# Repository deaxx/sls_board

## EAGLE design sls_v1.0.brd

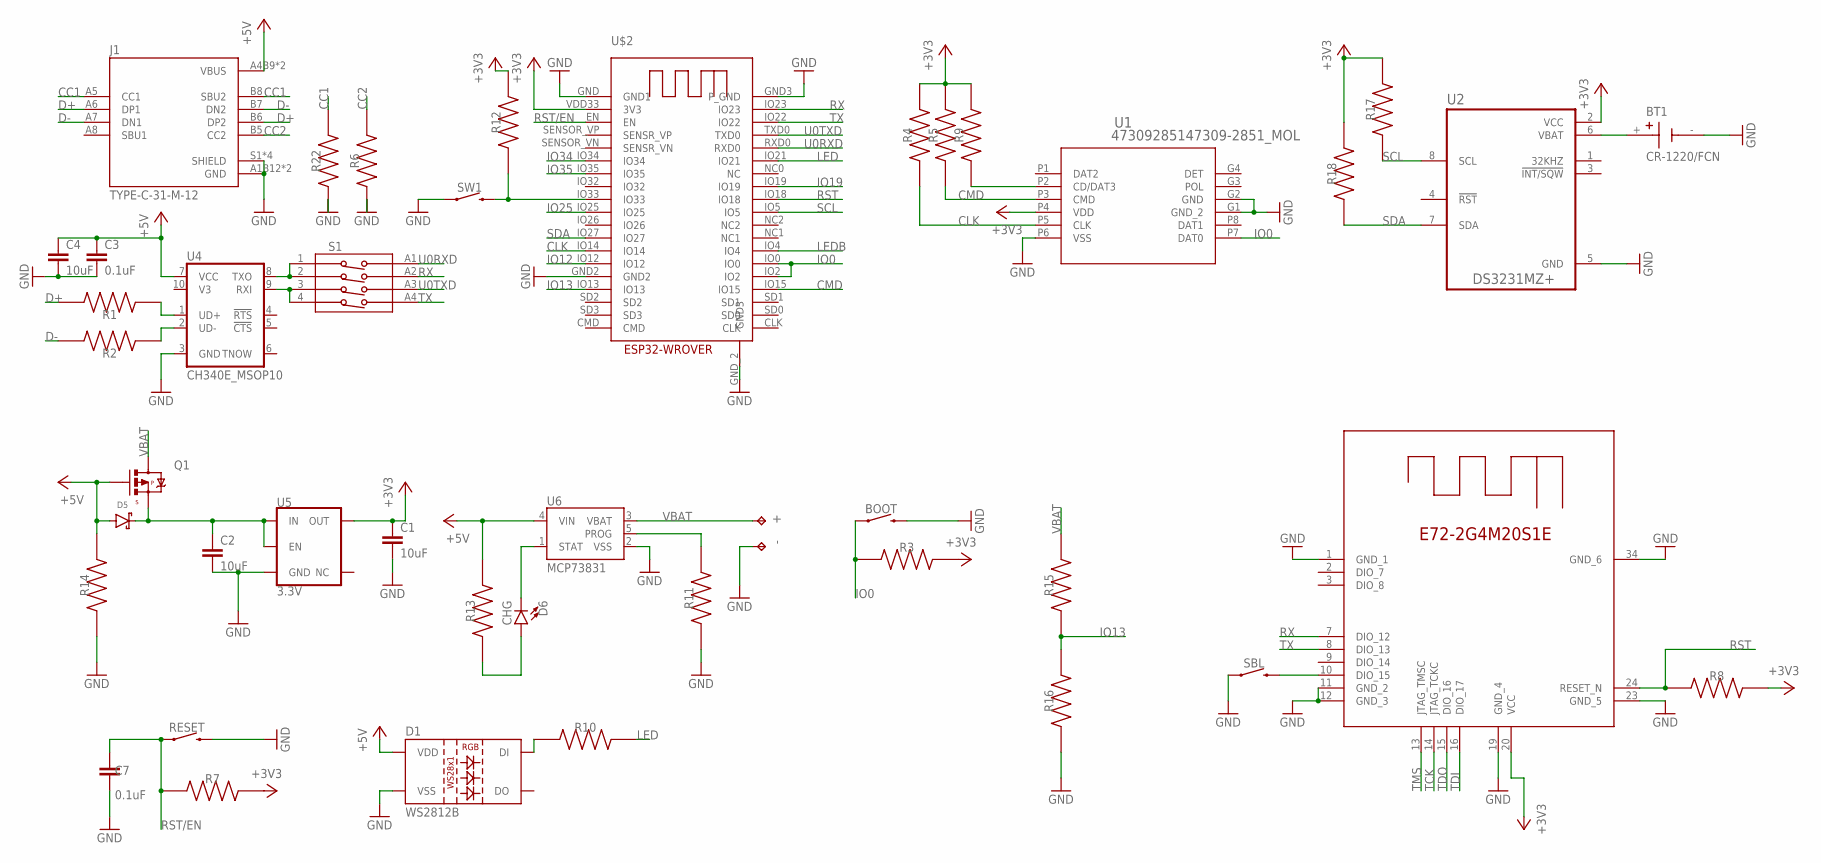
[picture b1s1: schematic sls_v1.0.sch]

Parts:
+: TPTP14R; TP14R
-: TPTP14R; TP14R
BOOT: MOMENTARY-SWITCH-SPST-SMD-4.6X2.8MM; TACTILE_SWITCH_SMD_4.6X2.8MM
BT1: CR-1220/FCN; BAT_CR-1220/FCN
C1, C2: 10uF; 0805
C3, C7: 0.1uF; 0603
C4: 10uF; 0603
D1: WS2812B
D5: DIODE-SCHOTTKY; SOD-323
D6: CHG; LED-0603
J1: TYPE-C-31-M-12; HRO_TYPE-C-31-M-12
Q1: MOSFET-PCHANNEL; SOT23
R1, R2, R3, R4, R5, R7, R9, R10, R12, R13, R14, R15, R16, R17, R18: RC0402FR-073M6L; RESC1005X40N
R6, R22: 5.1k; RESC1005X40N
R8: 100k; RESC1005X40N
R11: 2.7k; RESC1005X40N
RESET: MOMENTARY-SWITCH-SPST-SMD-4.6X2.8MM; TACTILE_SWITCH_SMD_4.6X2.8MM
S1: 416131160804
SBL: MOMENTARY-SWITCH-SPST-SMD-4.6X2.8MM; TACTILE_SWITCH_SMD_4.6X2.8MM
SW1: MOMENTARY-SWITCH-SPST-SMD-4.6X2.8MM; TACTILE_SWITCH_SMD_4.6X2.8MM
U1: 47309285147309-2851_MOL; 47309-2851_MOL
U2: DS3231MZ+; SOIC127P600X175-8N
U4: CH340E_MSOP10; MSOP10
U5: 3.3V; SOT23-5
U6: MCP73831; SOT23-5
U$1: E72-2G4M20S1E
U$2: ESP32-WROVER

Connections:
+3V3: C1.1, R3.2, R4.2, R5.2, R7.2, R8.2, R9.2, R12.2, R17.2, R18.2, U1.P4 (VDD), U2.2 (VCC), U5.5 (OUT), U$1.20 (VCC), U$2.VDD33 (3V3)
+5V: C3.1, C4.1, D1.1 (VDD), D5.A, J1.A4B9 (VBUS), J1.B4A9 (VBUS), Q1.1 (G), R13.2, R14.2, U4.7 (VCC), U6.4 (VIN)
CC1: J1.A5 (CC1), J1.B8 (SBU2), R22.2
CC2: J1.B5 (CC2), R6.2
CLK: R4.1, U1.P5 (CLK), U$2.IO14
CMD: R5.1, U1.P3 (CMD), U$2.IO15
D+: J1.A6 (DP1), J1.B6 (DP2), R1.2
D-: J1.A7 (DN1), J1.B7 (DN2), R2.2
GND: -.TP, BOOT.3 (2), BOOT.4 (2), BT1.-, C1.2, C2.2, C3.2, C4.2, C7.2, D1.3 (VSS), J1.A1B12 (GND), J1.B1A12 (GND), J1.S1 (SHIELD), J1.S2 (SHIELD), J1.S3 (SHIELD), J1.S4 (SHIELD), R6.1, R11.1, R14.1, R16.1, R22.1, RESET.3 (2), RESET.4 (2), SBL.1, SBL.2 (1), SW1.1, SW1.2 (1), U1.G1 (GND_2), U1.G2 (GND), U1.P6 (VSS), U2.5 (GND), U4.3 (GND), U5.2 (GND), U6.2 (VSS), U$1.1 (GND_1), U$1.11 (GND_2), U$1.12 (GND_3), U$1.19 (GND_4), U$1.23 (GND_5), U$1.34 (GND_6), U$2.GND (GND1), U$2.GND2, U$2.GND3 (P_GND), U$2.GND_2 (GND3)
IO0: BOOT.1, BOOT.2 (1), R3.1, U1.P7 (DAT0), U$2.IO0, U$2.IO2
IO12: U$2.IO12
IO13: R15.1, R16.2, U$2.IO13
IO19: U$2.IO19
IO25: U$2.IO25
IO34: U$2.IO34
IO35: U$2.IO35
LED: R10.2, U$2.IO21
LEDB: U$2.IO4
unnamed: BT1.+, U2.6 (VBAT)
unnamed: R1.1, U4.1 (UD+)
unnamed: S1.1, S1.2, U4.8 (TXO)
unnamed: S1.3, S1.4, U4.9 (RXI)
unnamed: C2.1, D5.C, Q1.2 (S), U5.1 (IN), U5.3 (EN)
unnamed: R12.1, SW1.3 (2), SW1.4 (2), U$2.IO33
unnamed: R2.1, U4.2 (UD-)
unnamed: SBL.3 (2), SBL.4 (2), U$1.10 (DIO_15)
unnamed: R9.1, U1.P2 (CD/DAT3)
unnamed: R11.2, U6.5 (PROG)
unnamed: D6.A, R13.1
unnamed: D1.4 (DI), R10.1
unnamed: D6.C, U6.1 (STAT)
RST: R8.1, U$1.24 (RESET_N), U$2.IO18
RST/EN: C7.1, R7.1, RESET.1, RESET.2 (1), U$2.EN
RX: S1.A2, U$1.7 (DIO_12), U$2.IO23
SCL: R17.1, U2.8 (SCL), U$2.IO5
SDA: R18.1, U2.7 (SDA), U$2.IO27
TCK: U$1.14 (JTAG_TCKC)
TDI: U$1.16 (DIO_17)
TDO: U$1.15 (DIO_16)
TMS: U$1.13 (JTAG_TMSC)
TX: S1.A4, U$1.8 (DIO_13), U$2.IO22
U0RXD: S1.A1, U$2.RXD0
U0TXD: S1.A3, U$2.TXD0
VBAT: +.TP, Q1.3 (D), R15.2, U6.3 (VBAT)

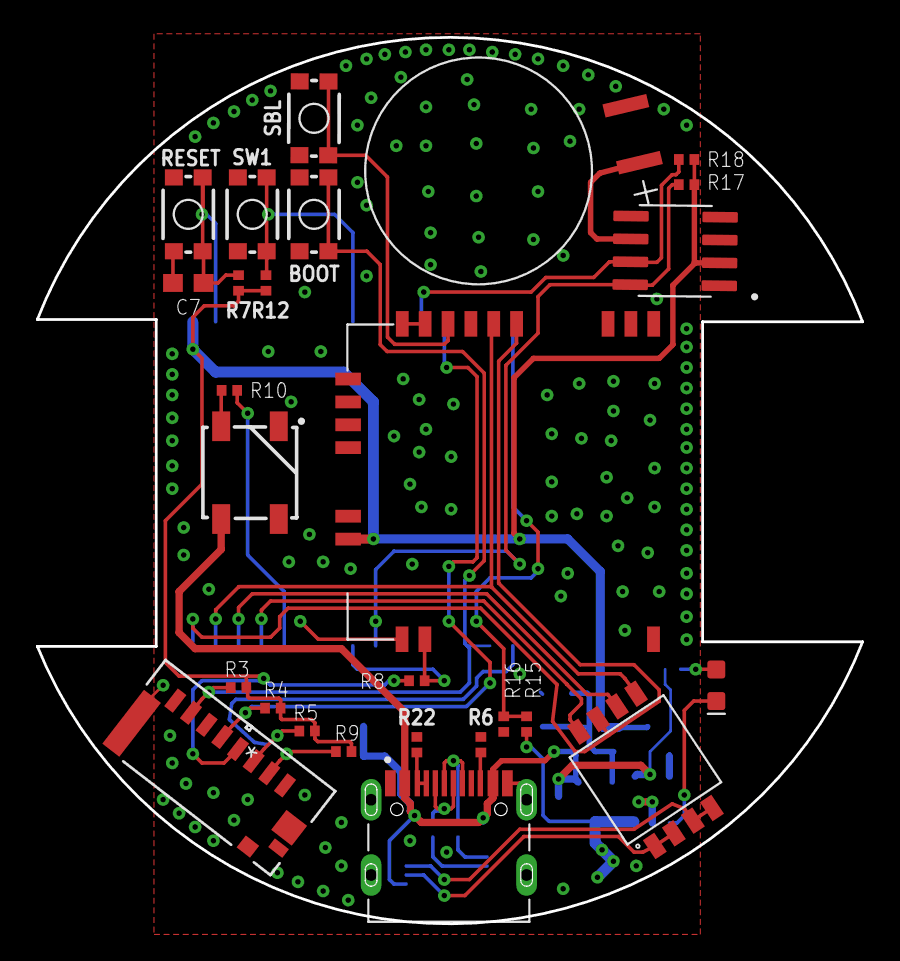
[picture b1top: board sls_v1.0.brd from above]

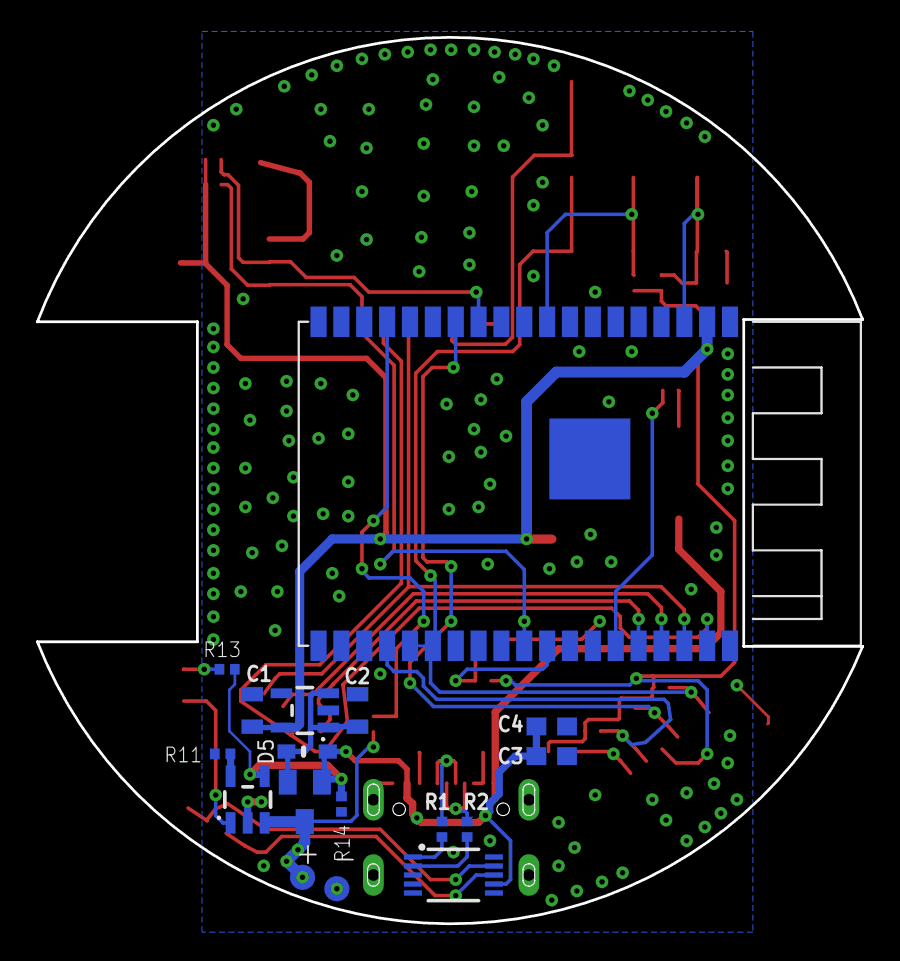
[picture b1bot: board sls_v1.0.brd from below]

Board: 2 copper layers, 45.8 x 49.2 mm, 44 parts (17 on the bottom side), 34 nets.

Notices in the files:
parts and their libraries:
SparkFun-Switches: Licensing: Creative Commons ShareAlike 4.0 International - https://creativecommons.org/licenses/by-sa/4.0
COPYRIGHT: Copyright (C) 2021 Ultra Librarian. All rights reserved.
